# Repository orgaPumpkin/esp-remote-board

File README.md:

# esp-remote-board
This is a custom board for my [esp-remote](https://github.com/orgaPumpkin/esp-remote-project) project (check it out).

It is a Hat for the esp8266, which contains an IR receiver, an IR emitter, and two buttons to send set messages.

I made this board in order to make this project more accessible, as putting the esp8266 into the Hat is way easier than connecting the components to a breadboard.

Additionally, a Hat is way more compact and clean than a breadboard and gives the project the feeling of a final product.

| Component             | Designator                        | LCSC Part Number | Link                                                  | Est Price |
|-----------------------|-----------------------------------|------------------|-------------------------------------------------------|-----------|
| TSOP34838             | U2                                | C44620           | https://www.aliexpress.com/item/1005005744020934.html | 2.2$      |
| PTS810                | SW3, SW4                          | C221895          | https://www.aliexpress.com/item/1005004443276452.html | 2.2$      |
| 470 Ohm 0402 resistor | R15, R16, R17, R18, R19, R20, R21 | C23179           | https://www.aliexpress.com/item/1005003721873929.html | 1.2$      |
| SS8050                | Q1                                | C2150            | https://www.aliexpress.com/item/1005008666448511.html | 0.9$      |
| 1x15 2.54 Socket      | J1, J2                            | C7499333         | https://www.aliexpress.com/item/4001198421663.html    | 1.5$      |
| 3.0mm THT IR LED      | D4, D5, D6, D7                    | C7470790         | https://www.aliexpress.com/item/1005003946239993.html | 2.1$      |
| 0603 red LED          | D3                                | C2286            | https://www.aliexpress.com/item/1005005226854182.html | 1.2$      |
| ESP8266 NodeMcu v2    |                                   | C503597          | https://www.aliexpress.com/item/32656401198.html      | 3.8$      |
|                       |                                   |                  |                                                       |           |
| AliExpress shipping   |                                   |                  |                                                       | 3$        |
| JLCPCB with shipping  |                                   |                  |                                                       | 28.2$     |
| Total ~               |                                   |                  |                                                       | 46.3$     |

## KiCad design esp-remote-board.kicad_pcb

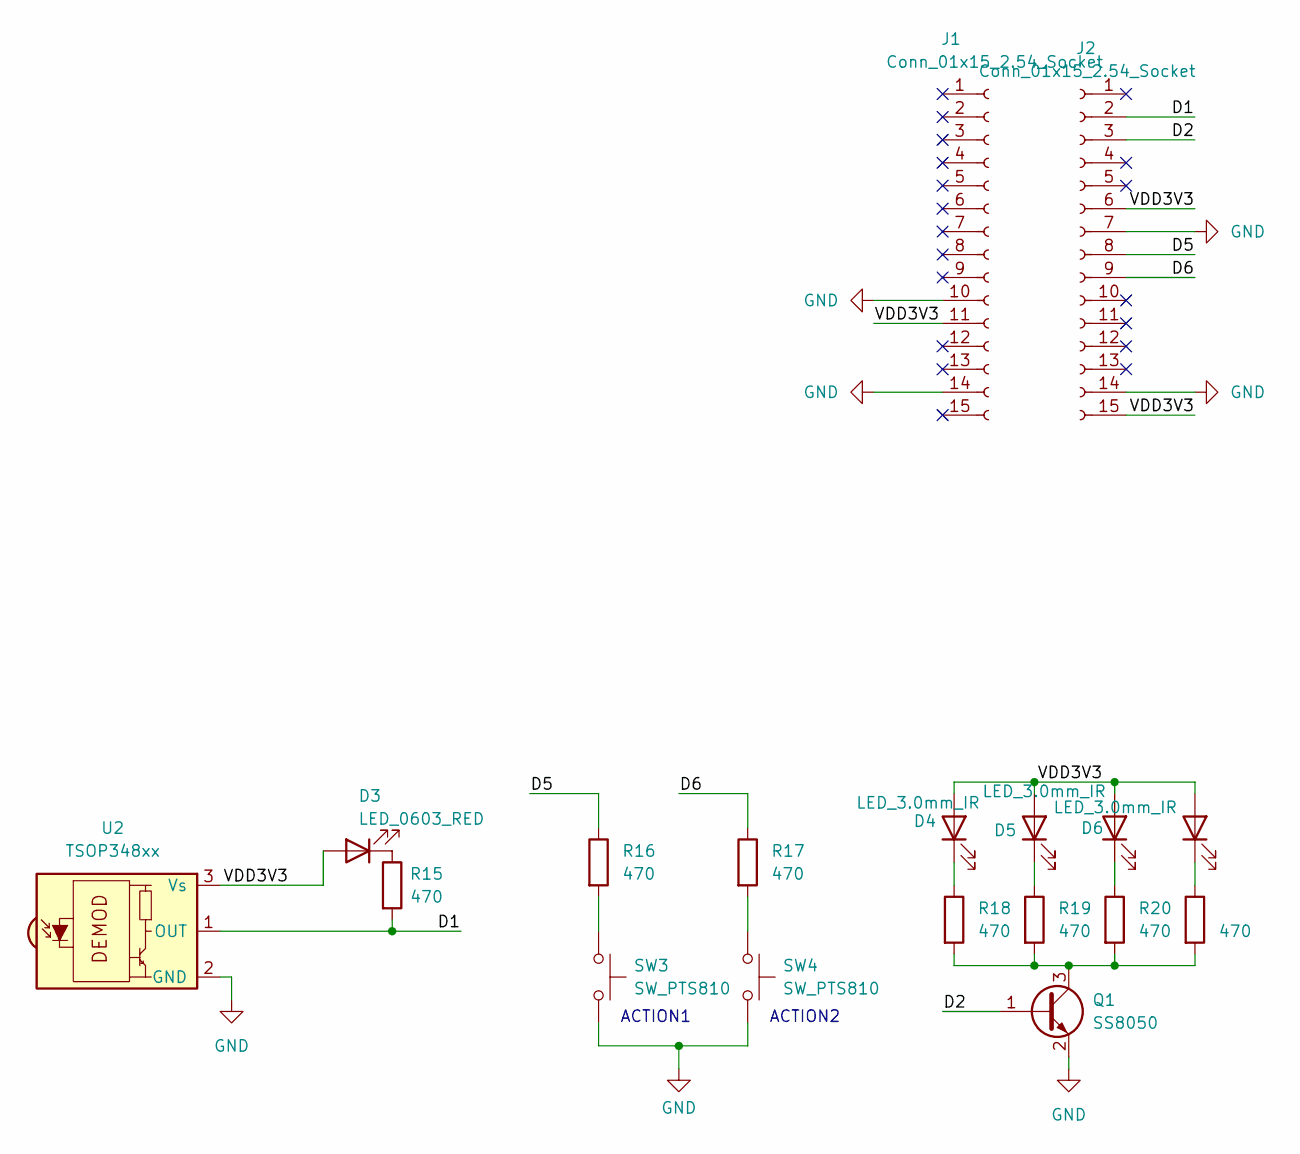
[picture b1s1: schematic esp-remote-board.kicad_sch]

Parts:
D3: LED_0603_RED; LED_0201_0603Metric; LCSC Part Number C2286
D4, D5, D6, D7: LED_3.0mm_IR; LED_D3.0mm; LCSC Part Number C7470790
J1, J2: Conn_01x15_2.54_Socket; PinSocket_1x15_P2.54mm_Vertical; LCSC Part Number C7499333
Q1: SS8050; SOT-23; LCSC Part Number C2150
R15, R16, R17, R18, R19, R20, R21: 470; R_0402_1005Metric; LCSC Part Number C23179
SW3, SW4: SW_PTS810; SW_SPST_PTS810; LCSC Part Number C221895
U2: TSOP348xx; Vishay_MOLD-3Pin; LCSC Part Number C44620

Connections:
/D1: J2.2, R15.2, U2.1 (OUT)
/D2: J2.3, Q1.1 (B)
/D5: J2.8, R16.1
/D6: J2.9, R17.1
/VDD3V3: D3.2 (A), D4.2 (A), D5.2 (A), D6.2 (A), D7.2 (A), J1.11, J2.6, J2.15, U2.3 (Vs)
GND: J1.10, J1.14, J2.7, J2.14, Q1.2 (E), SW3.2, SW4.2, U2.2 (GND)
unnamed: D3.1 (K), R15.1
unnamed: D4.1 (K), R18.1
unnamed: D5.1 (K), R19.1
unnamed: D6.1 (K), R20.1
unnamed: D7.1 (K), R21.1
unnamed: Q1.3 (C), R18.2, R19.2, R20.2, R21.2
unnamed: R16.2, SW3.1
unnamed: R17.2, SW4.1

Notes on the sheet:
ACTION2
ACTION1

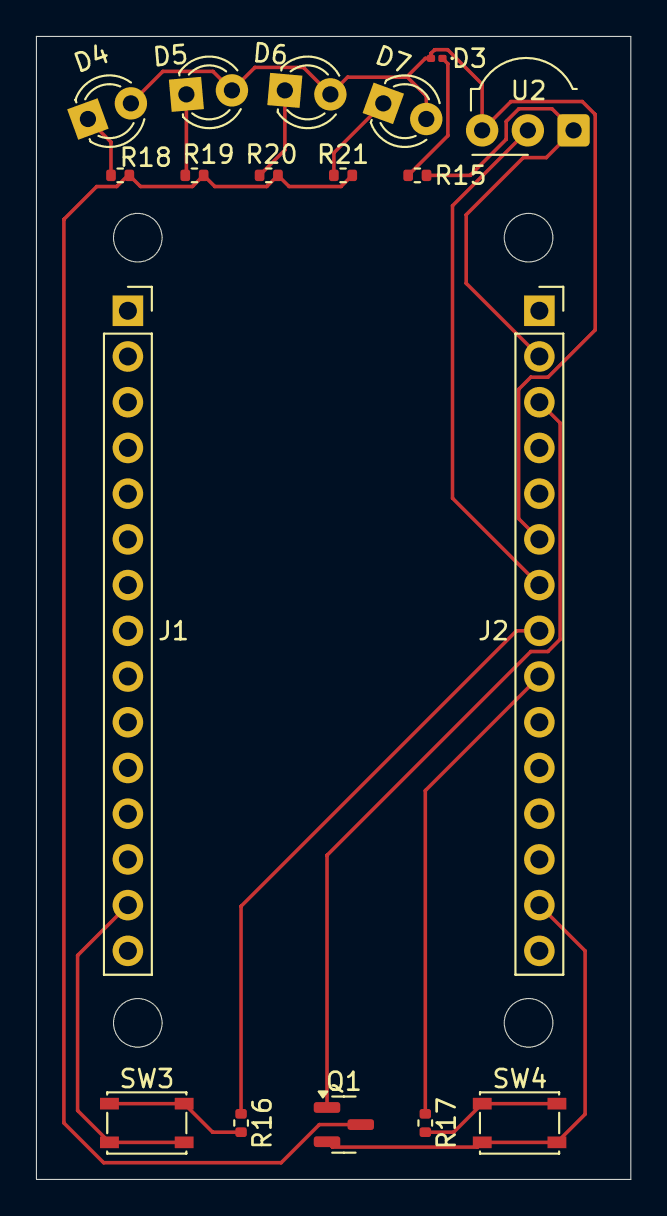
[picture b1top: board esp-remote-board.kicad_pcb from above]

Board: 2 copper layers, 33.0 x 63.5 mm, 18 parts (0 on the bottom side), 14 nets.

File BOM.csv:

Comment,Designator,Footprint,LCSC Part Number,Datasheet
TSOP348xx,U2,OptoDevice:Vishay_MOLD-3Pin,C44620,https://www.vishay.com/docs/82489/tsop322.pdf
SW_PTS810,SW4,Button_Switch_SMD:SW_SPST_PTS810,C221895,~
SW_PTS810,SW3,Button_Switch_SMD:SW_SPST_PTS810,C221895,~
470,R21,Resistor_SMD:R_0402_1005Metric,C23179,~
470,R20,Resistor_SMD:R_0402_1005Metric,C23179,~
470,R19,Resistor_SMD:R_0402_1005Metric,C23179,~
470,R18,Resistor_SMD:R_0402_1005Metric,C23179,~
470,R17,Resistor_SMD:R_0402_1005Metric,C23179,~
470,R16,Resistor_SMD:R_0402_1005Metric,C23179,~
470,R15,Resistor_SMD:R_0402_1005Metric,C23179,~
SS8050,Q1,Package_TO_SOT_SMD:SOT-23,C2150,http://www.secosgmbh.com/datasheet/products/SSMPTransistor/S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
Conn_01x15_2.54_Socket,J2,Connector_PinSocket_2.54mm:PinSocket_1x15_P2.54mm_Vertical,C7499333,~
Conn_01x15_2.54_Socket,J1,Connector_PinSocket_2.54mm:PinSocket_1x15_P2.54mm_Vertical,C7499333,~
LED_3.0mm_IR,D7,LED_THT:LED_D3.0mm,C7470790,~
LED_3.0mm_IR,D6,LED_THT:LED_D3.0mm,C7470790,~
LED_3.0mm_IR,D5,LED_THT:LED_D3.0mm,C7470790,~
LED_3.0mm_IR,D4,LED_THT:LED_D3.0mm,C7470790,~
LED_0603_RED,D3,LED_SMD:LED_0201_0603Metric,C2286,~

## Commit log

2025-06-20 create basic mcu schematic
2025-06-20 Add IR input and output, and 2 action buttons
2025-06-22 create initial placment
2025-06-23 remake as hat
2025-06-23 redo margins and routing, now uses only one layer
2025-07-03 Add production files
2025-07-03 Clean, format, and add the journal
2025-07-03 Add the pictures to the journal
2025-07-03 Add README
2025-07-04 Add the esp to the BOM
2025-07-04 Add the schematic to the readme
2025-07-05 Link BOM to aliexpress and add price estimates
